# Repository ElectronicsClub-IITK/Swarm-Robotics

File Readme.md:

# Swarm Robotics 

## Introduction 

This is the Code base of the Project Swarm Robotics of Electronics club. This is a Summer Project that has been undertaken in the Summer of 2024.

### Project Overview 

The Project involved developing an infrastructure of Swarm Robots that can be used in several use cases with minimal modifications in their Design and Circuitry. 
We are designing a Multi-Terrain Robot that can maneuver in any terrain and gather critical information. 
- Developing an in-house PCB
- Developing an IMU based localization system
- Developing a system of connecting various such small robots to a mother bot.

## WEEK 0

In week 0, basics of python and python assignment is done. Also, git and github is covered. 
We’re using Git and GitHub as tools for version control, collaboration and project management, thus ensuring everyone can work together efficiently.  

## WEEK 1

### Microcap
In week 1, we started with the microcap. Micro-Cap is used for the analysis and simulation of various circuits. Multiple circuits are analyzed for familiarity with Micro-Cap. Simulation of the circuit where the transistor works as a switch was done on Micro-Cap for verification and to ensure proper working.
### Solidworks - Assignment I
SolidWorks is instrumental in building the Swarm Robot by enabling detailed 3D modeling and design of mechanical components, ensuring precise fits and functionality. 
It allows for comprehensive simulation and analysis of movement, stress, and performance, helping to identify and resolve potential issues early.

##  WEEK 2

### KiCad
KiCad is a powerful and open-source EDA software, used for designing circuit schematics and PCBs. It is used to create detailed schematics that include all components, such as micro-controllers, sensors, actuators, and communication modules.
###  Solidworks - Assignment II
SolidWorks is being used for the rough designing of the 3D model of our car. It assists in analysing weight and design of the swram robotics model efficiently.
This reduces errors and optimizes the design before actual prototyping and manufacturing, saving time and resources.

## WEEK 3

### KALMAN FILTER
Kalman filtering (KF) is an optimal estimation algorithm that provides estimates of some unknown variables given the measurements observed over time.
The gyroscope provides the angular velocity and accelerometers provide linear acceleration . We then combine these two data to improve accuracy by implementing KF.
### GNSS-INS Stimulation
GNSS-INS-SIM is an GNSS/INS simulation project, which generates reference trajectories, IMU sensor output, GPS output, odometer output and magnetometer output.
It allows users to model and test their algorithms in different scenarios, providing a flexible platform for developing and validating navigation solutions without needing extensive field tests.
### PCB Design
In our project, we use KiCad to design PCBs that integrate motor driver ICs (e.g., L298) with microcontrollers and other components. In robotics we require microcontrollers to process data and control actuators. Using KiCad, we can design custom microcontroller boards (Arduino nano 33 IoT) that meet specific requirements. We can make our own symbols and can add appropriate footprints to them.
### ROS and Controls
ROS (Robot Operating System) is an open-source, flexible framework for writing robot software. The project involves the coordination of multiple robots to perform tasks in a decentralized manner. A robot in the swarm operates based on local information and interactions with its neighbors.

Resources : 
ETH Zurich’s Programming for Robotics - ROS
Robotics Back End - ROS Noetic For Beginners

## WEEK 4

### PCB Design - BMS
Motors generally require more current than the Arduino can safely provide. So we are going to use an external power source for motors. We will be using BMS for providing required power to arduino as well as motors and use transistor (NMOS) as a switch.

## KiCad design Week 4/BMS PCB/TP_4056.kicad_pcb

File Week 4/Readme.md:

# Week -4

## BMS PCB
A PCB for the BMS of a LiPo battery made by Diya Motagi

## Design of the Bot
The Final Iterations of Design made by Surya Shukla, Samarth, Abhay and Mayank. The Files are in Solid Works 

## GNSS INS Simulator
This Directory Contains the code for Kalman filter on the GNSS INS Simulator by Dakshith, Krishna and Samarth

## IMU Based Localisation using Kalman Filter 

This Directory Contains the code for IMU Based Localisation using Kalman Filter by Shreyas and Akshat Jain.

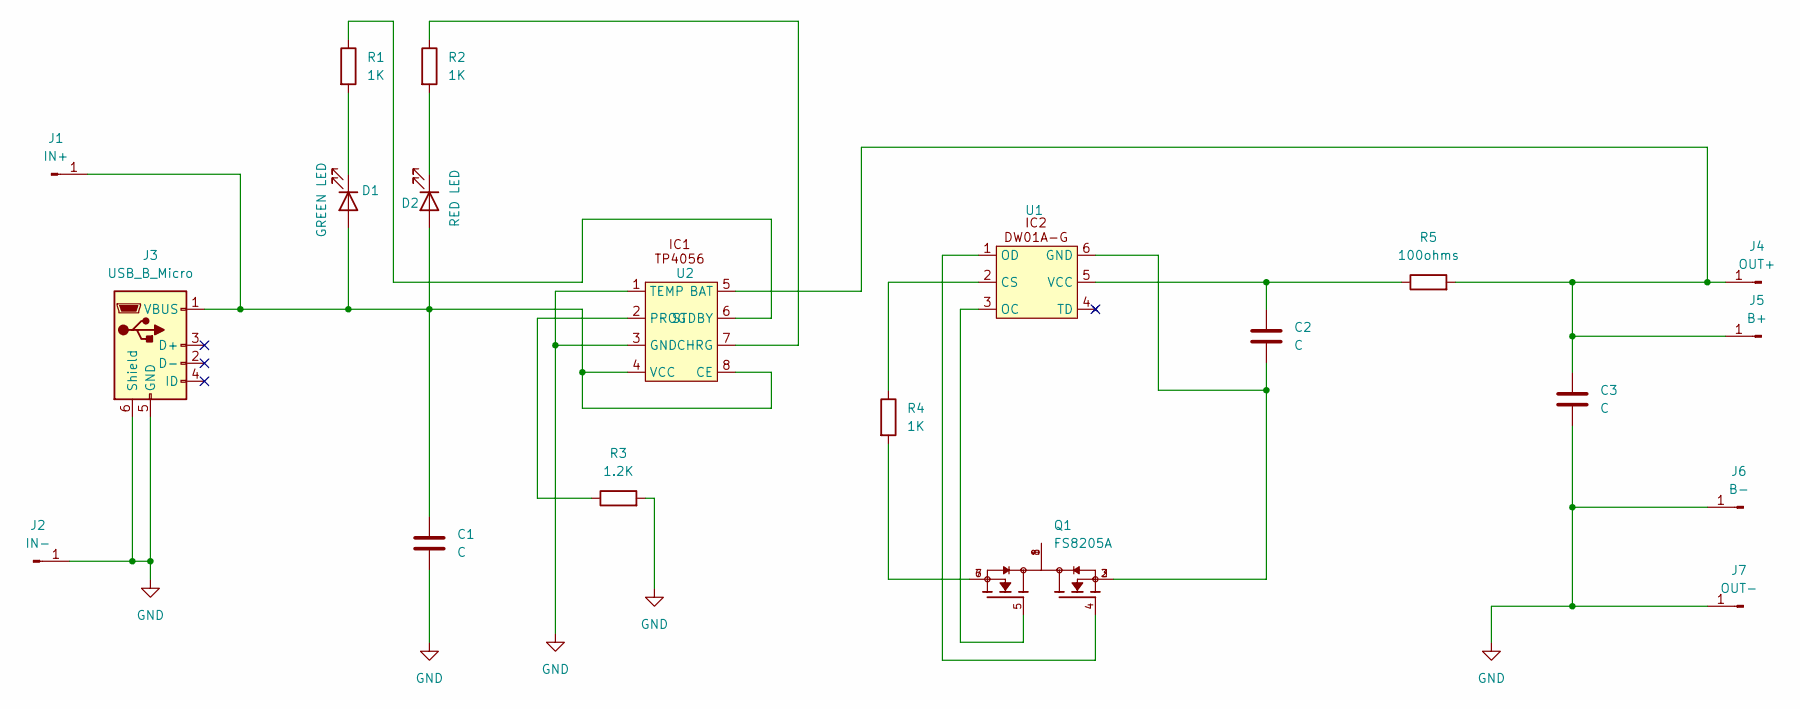
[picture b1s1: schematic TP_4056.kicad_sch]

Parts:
C1, C2, C3: C; C_0201_0603Metric
D1: GREEN LED; LED_0201_0603Metric
D2: RED LED; LED_0201_0603Metric
J1: IN+; SolderWire-0.75sqmm_1x01_D1.25mm_OD2.3mm
J2: IN-; SolderWire-0.75sqmm_1x01_D1.25mm_OD2.3mm
J3: USB_B_Micro; USB_Micro-B_Molex_47346-0001
J4: OUT+; SolderWire-0.75sqmm_1x01_D1.25mm_OD2.3mm
J5: B+; SolderWire-0.75sqmm_1x01_D1.25mm_OD2.3mm
J6: B-; SolderWire-0.75sqmm_1x01_D1.25mm_OD2.3mm
J7: OUT-; SolderWire-0.75sqmm_1x01_D1.25mm_OD2.3mm
Q1: FS8205A; SOP65P640X120-8N; PARTREV 1.7
R1, R2, R4: 1K; R_0201_0603Metric
R3: 1.2K; R_0201_0603Metric
R5: 100ohms; R_0201_0603Metric
U1: SOT-23-6
U2: SOP-8_3.9x4.9mm_P1.27mm

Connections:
GND: C1.2, C3.2, J2.1, J3.5 (GND), J3.6 (Shield), J6.1, J7.1, R3.2, U2.1 (TEMP), U2.3 (GND)
unnamed: C1.1, D1.2 (A), D2.2 (A), J1.1, J3.1 (VBUS), U2.4 (VCC), U2.8 (CE)
unnamed: D1.1 (K), R1.2
unnamed: D2.1 (K), R2.2
unnamed: C3.1, J4.1, J5.1, R5.2, U2.5 (BAT)
unnamed: Q1.1, Q1.8
unnamed: Q1.6, Q1.7, R4.2
unnamed: R4.1, U1.2 (CS)
unnamed: C2.2, Q1.2, Q1.3, U1.6 (GND)
unnamed: Q1.5, U1.3 (OC)
unnamed: Q1.4, U1.1 (OD)
unnamed: C2.1, R5.1, U1.5 (VCC)
unnamed: R2.1, U2.7 (CHRG)
unnamed: R3.1, U2.2 (PROG)
unnamed: R1.1, U2.6 (STDBY)

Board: 2 copper layers, 20 parts (0 on the bottom side), 15 nets, no tracks yet.

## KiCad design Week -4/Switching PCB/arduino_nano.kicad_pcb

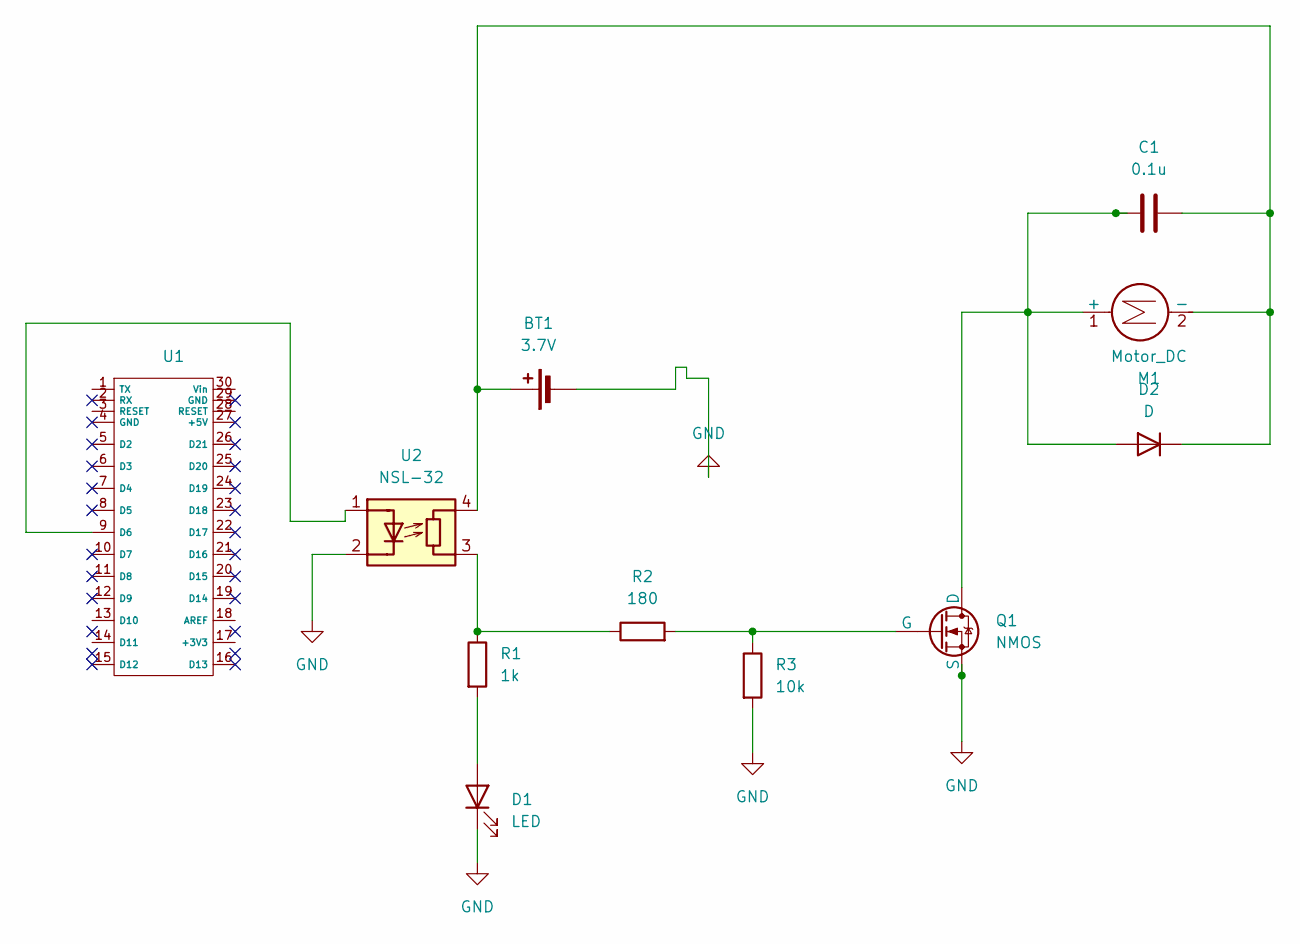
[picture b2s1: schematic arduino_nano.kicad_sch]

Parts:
BT1: 3.7V; JWT_A3963_1x02_P3.96mm_Vertical
C1: 0.1u; C_0201_0603Metric
D1: LED; LED_D3.0mm_IRGrey
D2: D; D_1206_3216Metric_Pad1.42x1.75mm_HandSolder
M1: Motor_DC; JWT_A3963_1x02_P3.96mm_Vertical
Q1: NMOS; TO-92L_HandSolder
R1: 1k; R_0805_2012Metric_Pad1.20x1.40mm_HandSolder
R2: 180; R_0805_2012Metric_Pad1.20x1.40mm_HandSolder
R3: 10k; R_0805_2012Metric_Pad1.20x1.40mm_HandSolder
U1: Arduino_Nano_WithMountingHoles
U2: NSL-32; Luna_NSL-32

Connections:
GND: BT1.2 (-), D1.1 (K), Q1.3 (S), R3.2, U2.2 (K)
unnamed: BT1.1 (+), C1.2, D2.1 (K), M1.2 (-), U2.4 (R)
unnamed: D1.2 (A), R1.2
unnamed: C1.1, D2.2 (A), M1.1 (+), Q1.1 (D)
unnamed: Q1.2 (G), R2.2, R3.1
unnamed: R1.1, R2.1, U2.3 (R)
unnamed: U1.9 (D6), U2.1 (A)

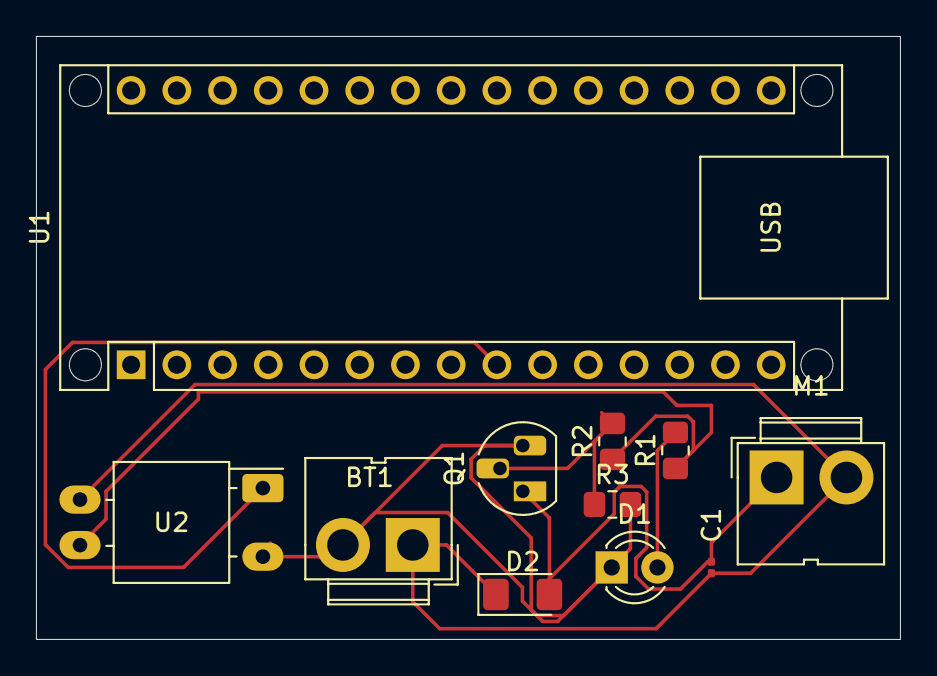
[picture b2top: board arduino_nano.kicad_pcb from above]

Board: 2 copper layers, 48.0 x 33.5 mm, 11 parts (0 on the bottom side), 7 nets.

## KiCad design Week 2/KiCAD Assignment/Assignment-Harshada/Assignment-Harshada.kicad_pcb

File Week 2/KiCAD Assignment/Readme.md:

# TP4056 based Battery Charging Circuit Design 

Lipo battery charging circuits are very important for many applications and are extremely useful in many cases. 

TP4056 is one of the Most Common IC and hence you are tasked to design a circuit for the BMS of Lipo battery

For more on Lipo Batteries refer https://rogershobbycenter.com/lipoguide  <br>
- The Schematic of the circuit has been given in this folder
- Refer to the Datasheet (PDF File in this folder)
- Design a PCB by assigning footprints (Ensure that they are hand solderable)
- Route with default settings 
- Check for the package of IC and find the footprint

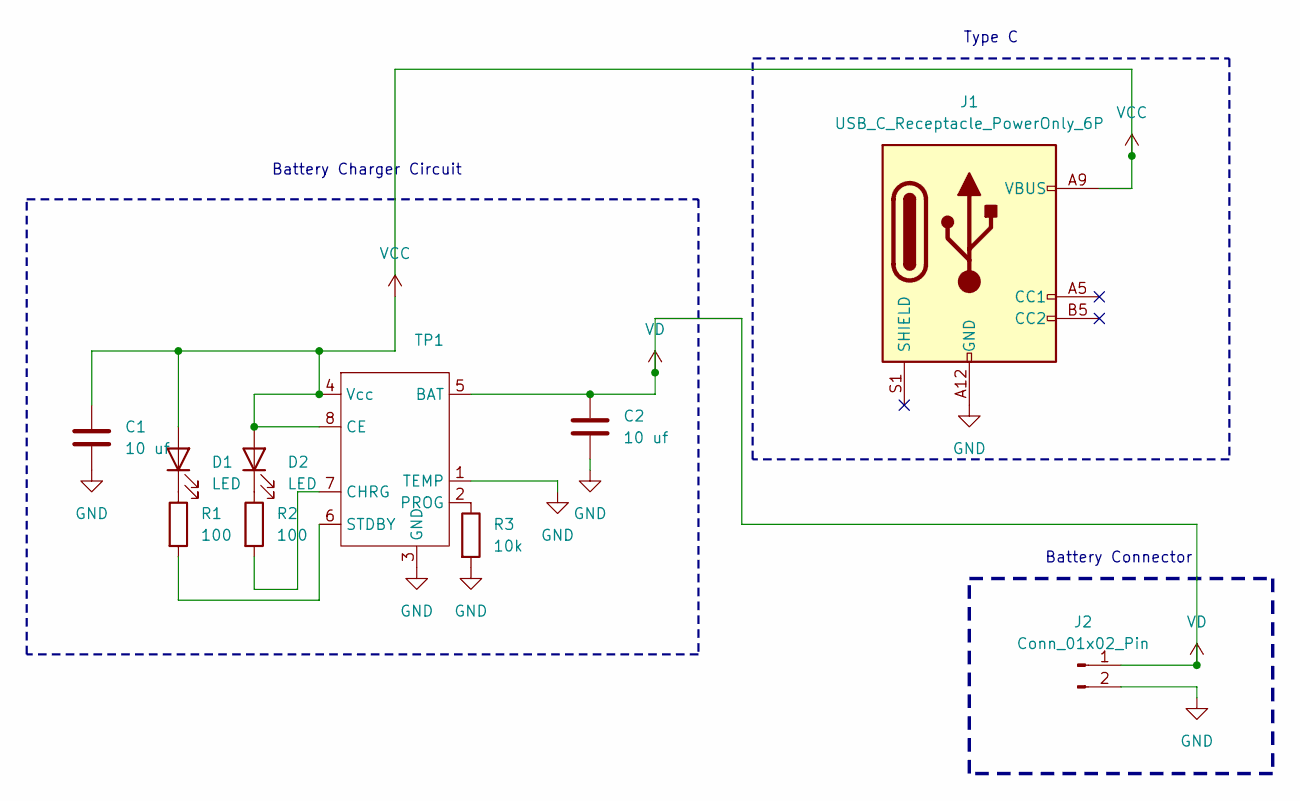
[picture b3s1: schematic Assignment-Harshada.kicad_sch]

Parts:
C1, C2: 10 uf; C_1206_3216Metric
D1, D2: LED; LED_D3.0mm
J1: USB_C_Receptacle_PowerOnly_6P; USB_C_Receptacle_GCT_USB4135-GF-A_6P_TopMnt_Horizontal
J2: Conn_01x02_Pin; PinHeader_1x02_P1.00mm_Vertical_SMD_Pin1Left
R1, R2: 100; R_1206_3216Metric
R3: 10k; R_1206_3216Metric
TP1: SOP-8_3.9x4.9mm_P1.27mm

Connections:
GND: C1.2, C2.2, J1.A12 (GND), J1.B12 (GND), J2.2, R3.2, TP1.1 (TEMP), TP1.3 (GND)
unnamed: D1.1 (K), R1.1
unnamed: D2.1 (K), R2.1
unnamed: R2.2, TP1.7 (CHRG)
unnamed: R3.1, TP1.2 (PROG)
unnamed: R1.2, TP1.6 (STDBY)
VCC: C1.1, D1.2 (A), D2.2 (A), J1.A9 (VBUS), J1.B9 (VBUS), TP1.4 (Vcc), TP1.8 (CE)
VD: C2.1, J2.1, TP1.5 (BAT)

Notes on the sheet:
Battery Charger Circuit
Type C
Battery Connector

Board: 2 copper layers, 10 parts (0 on the bottom side), 8 nets, no tracks yet.

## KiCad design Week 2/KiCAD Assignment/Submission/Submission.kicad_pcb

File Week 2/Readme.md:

<<<<<<< HEAD
# Week 2
=======
# Week -2

## KiCAD Assignment
This folder contains materials and assignments related to KiCAD.

### Files
- [Assignment.kicad_sch](KiCAD%20Assignment/Assignment.kicad_sch)
- [Readme.md](KiCAD%20Assignment/Readme.md)
- [TP4056.pdf](KiCAD%20Assignment/TP4056.pdf)

## Solidworks Assignment 1
This folder contains the first Solidworks assignment.

### Files
- [Readme.md](Solidworks%20Assignment%201/Readme.md)

## Solidworks Assignment 2
This folder contains the second Solidworks assignment.

### Files
- [Readme.md](Solidworks%20Assignment%202/Readme.md)
>>>>>>> 5a61ac3fd45ec20d82bd862766978928fd88a5e5

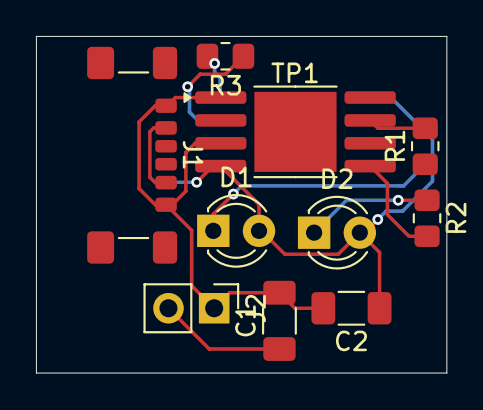
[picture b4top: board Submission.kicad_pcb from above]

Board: 2 copper layers, 22.8 x 18.7 mm, 10 parts (0 on the bottom side), 8 nets.

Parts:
C1, C2: 10 uf; C_1206_3216Metric_Pad1.33x1.80mm_HandSolder
D1, D2: LED; LED_D3.0mm
J1: USB_C_Receptacle_PowerOnly_6P; USB_C_Receptacle_GCT_USB4135-GF-A_6P_TopMnt_Horizontal
J2: Conn_01x02; PinHeader_1x02_P2.54mm_Vertical
R1, R2: 100; R_0805_2012Metric_Pad1.20x1.40mm_HandSolder
R3: 10k; R_0805_2012Metric_Pad1.20x1.40mm_HandSolder
TP1: SOP-8-1EP_4.57x4.57mm_P1.27mm_EP4.57x4.45mm

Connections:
GND: C1.2, C2.2, J1.A12 (GND), J1.B12 (GND), J2.1, R3.2, TP1.1 (TEMP), TP1.3 (GND)
unnamed: D1.1 (K), R1.1
unnamed: D2.1 (K), R2.1
unnamed: R1.2, TP1.7 (CHRG)
unnamed: R3.1, TP1.2 (PROG)
unnamed: R2.2, TP1.5 (STDBY)
VCC: C2.1, D1.2 (A), D2.2 (A), J1.A9 (VBUS), J1.B9 (VBUS), TP1.4 (Vcc), TP1.8 (CE)
VD: C1.1, J2.2

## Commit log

2024-05-07 Adding Python Assignment
2024-05-07 Objects and Data Structures
2024-05-07 Chained Comparison Operators
2024-05-07 Statements Assessment
2024-05-07 Functions and Methods
2024-05-08 Assignment 1
2024-05-08 Adding ML Assignment
2024-05-08 Assigment submission
2024-05-09 python assign
2024-05-09 first assign python
2024-05-09 Added all 4 completed assignments
2024-05-09 Submiting asst
2024-05-09 python assignment completed
2024-05-09 python assignment competed
2024-05-11 Python_Assignment
2024-05-11 python_assignment_Diya
2024-05-12 Uploading Analog Content
2024-05-12 Small Signal Analysis
2024-05-13 Analog Assignment Submission
2024-05-13 Analog_Submission_Kshitij
2024-05-13 Added Screenshots
2024-05-13 Adding Screenshots
2024-05-13 ElectronicsAssignment
2024-05-13 Rename Screenshot 2024-05-13 232252.png to AC_Analysis
2024-05-15 Updating Soildworks Assignment
2024-05-18 Updating Week 2
2024-05-19 Solidworks Assignment 1
2024-05-19 Solidworks Assignment 2
2024-05-20 solidworks_assignment1_cannon
2024-05-20 SolidWorks_Assignment_Kshitij
2024-05-20 KiCAD_Assignment_Kshitij
2024-05-20 KiCad Assignment
2024-05-20 solidworks_assignment2_slider_crank
2024-05-20 Ruchika_Kicad assignment
2024-05-21 Kicad Assignment Completed
2024-05-24 Adding Week 3
2024-06-07 Adding PCB and Week 4
2024-06-07 Organising the Repo
2024-06-08 Adding Part files
